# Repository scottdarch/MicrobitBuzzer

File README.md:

# MicrobitBuzzer
A somewhat loud speaker for use with the [BBC Microbit](http://microbit.org/).

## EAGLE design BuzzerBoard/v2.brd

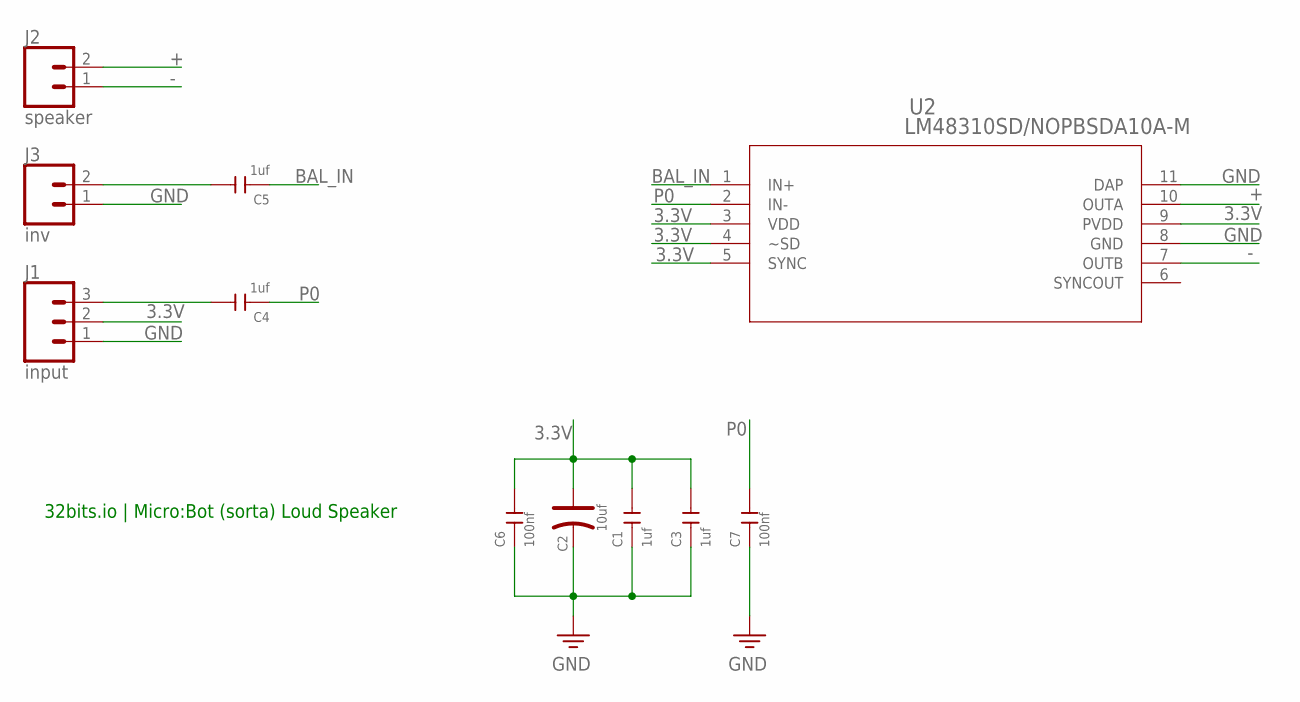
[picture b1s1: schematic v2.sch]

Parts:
C1, C3, C4, C5: 1uf; C0603
C2: 10uf; PC-D5.3MM
C6, C7: 100nf; C0603
J1: input; 1X03_SMD_RA_MALE
J2: speaker; 1X02
J3: inv; 1X02
U2: LM48310SD/NOPBSDA10A-M; SDA10A-M

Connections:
3.3V: C1.2, C2.+, C3.2, C6.2, J1.2, U2.3 (VDD), U2.4 (~SD), U2.5 (SYNC), U2.9 (PVDD)
+: J2.2, U2.10 (OUTA)
-: J2.1, U2.7 (OUTB)
BAL_IN: C5.1, U2.1 (IN+)
BAL_IN_RAW: C5.2, J3.2
GND: C1.1, C2.-, C3.1, C6.1, C7.1, J1.1, J3.1, U2.8 (GND), U2.11 (DAP)
P0: C4.1, C7.2, U2.2 (IN-)
P0_RAW: C4.2, J1.3

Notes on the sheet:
32bits.io | Micro:Bot (sorta) Loud Speaker

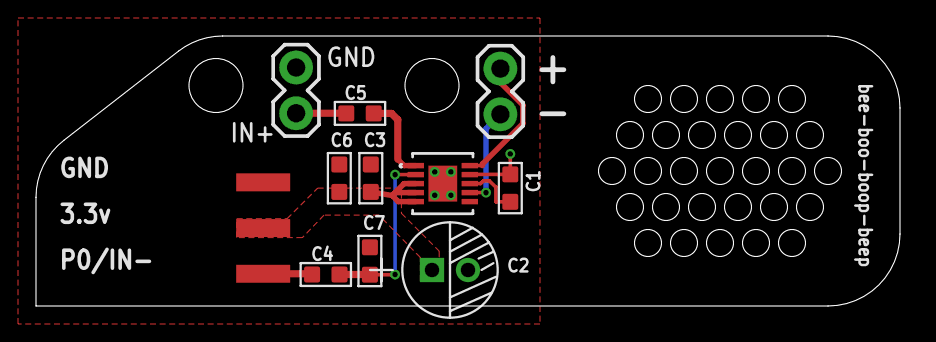
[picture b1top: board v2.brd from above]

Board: 2 copper layers, 48.0 x 15.0 mm, 12 parts (1 on the bottom side), 8 nets.

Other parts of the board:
U$2: 32BITS_LOGO

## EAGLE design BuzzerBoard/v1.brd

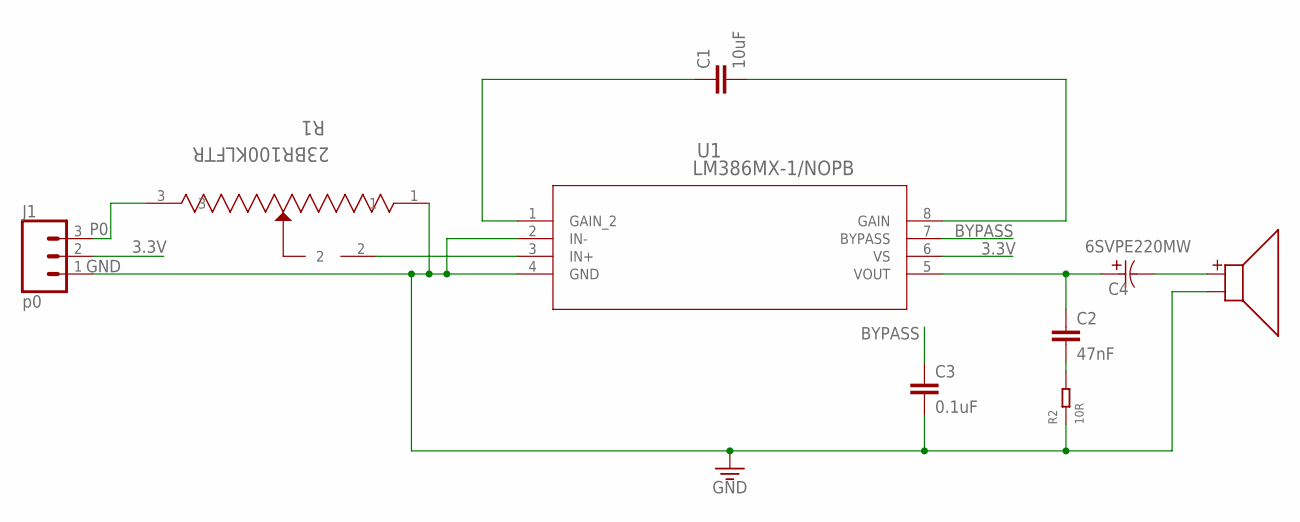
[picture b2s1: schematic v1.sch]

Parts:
C1: 10uF; 0603
C2: 47nF; 0603
C3: 0.1uF; 0603
C4: 6SVPE220MW; PCAP_SVP_B6
J1: p0; 1X03_SMD_RA_MALE
R1: 23BR100KLFTR; SOT_23BR100KLFTR
R2: 10R; R0603
U1: LM386MX-1/NOPB; M08A
U$1: SMS-1308MS-2-R

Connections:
3.3V: J1.2, U1.6 (VS)
+: C4.2 (22), U$1.+
BYPASS: C3.1, U1.7 (BYPASS)
GAIN: C1.2, U1.8 (GAIN)
GND: C3.2, J1.1, R1.1, R2.1, U1.2 (IN-), U1.4 (GND), U$1.-
IN+: R1.2, U1.3 (IN+)
unnamed: C2.2, R2.2
unnamed: C1.1, U1.1 (GAIN_2)
P0: J1.3, R1.3
VOUT: C2.1, C4.1 (11), U1.5 (VOUT)

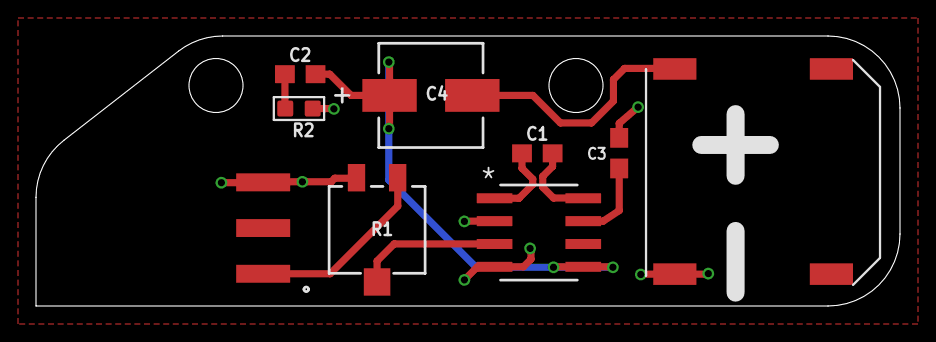
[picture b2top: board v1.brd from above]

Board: 2 copper layers, 48.0 x 15.0 mm, 10 parts (1 on the bottom side), 10 nets.

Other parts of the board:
U$2: 32BITS_LOGO

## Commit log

2017-10-31 Starting Buzzer Board
2017-11-02 Initial schematic capture.
2017-11-03 V1 to OSH park.
2017-11-11 Adding pdf of schematic and board.
2017-11-14 Schmatic cleanup + datasheet.
2017-11-16 starting on v2
2017-11-17 progress on the v2 board
2017-11-18 Switching to LM48310 on the v2 board.
2017-11-18 Huck wants to use this computer, dammit.
2017-11-18 V2 to oshpark.
2017-11-28 Stashing Girl Scout hex image in this repo

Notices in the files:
parts and their libraries:
SparkFun-Capacitors: Licensing: Creative Commons ShareAlike 4.0 International - https://creativecommons.org/licenses/by-sa/4.0
